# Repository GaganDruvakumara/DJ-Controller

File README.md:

# DIY DJ CONTROLLER
<body1 align="center">
  <br>

  <br>
  I’ve wanted to get into this hobby for a while, but the cost of entry was a major barrier. I looked through existing projects online, but I couldn’t find any open-source DJ controllers that really stood out. Many were small, limited, or designed more like experimental gadgets rather than something practical for real DJ use. There seemed to be a gap between expensive commercial controllers and accessible open-source alternatives, which inspired me to create this project.
  <br>
  <br>
  <i>This project is a fully open-source, 4-channel DIY DJ controller designed to be a functional and customizable alternative for anyone interested in building their own hardware.</i>
</body1>

# Key Features
* 4 Channel Deck
* XLR & 6.35MM Jack L&R master out + 3.5mm Jack L+R master out
* 3.5mm Jack headphone out
* 32-bit DAC for outputs
* 2 Neutrik Jack Mic Inputs
* 24-bit ADC for inputs
* 16 performance pad with mode selector
* 2 rotary encoders for menu navigation

# PCB
7x 2-layer PCBs (9 total including duplicates) designed in KiCad
### PCB Schematic

### PCB Front Layer

### PCB Back Layer

### PCB 3D View
Component models from GrabCad

## PCB Wiring Schematic

# CAD Assembly
CAD models designed in [Onshape](https://cad.onshape.com/documents/7791953f15b9474113af6284/w/087eac69f09fbec4411ed0d8/e/f1a33f0f3682f52a7b10a5d9?renderMode=0&uiState=6a372b9190a847a714621490).
Assembly done with M3x5x5 threaded inserts & M3 screws. Countersunk screws are used to attach the backplate, otherwise use pan head screws for everything else.

# Bill of Materials

|Part                                       |Min Qty.|Price Per Order|Approx. Cost|Link                                                |
|-------------------------------------------|--------|---------------|------------|----------------------------------------------------|
|                                           |        |               |            |                                                    |
|**Electronic Components**                      |        |               |            |                                                    |
|                                           |        |               |            |                                                    |
|Raspberry Pi Pico                          |1       |$3.00          |$3.00       |https://www.aliexpress.us/item/3256805941727857.html|
|MCP23017 I2C GPIO Expander                 |3       |$1.50          |$4.50       |https://www.aliexpress.us/item/3256809349179807.html|
|CD74HC4067M Multiplexer                    |2       |$4.00          |$4.00       |https://www.aliexpress.us/item/3256810617508863.html|
|PCM5012 Module                             |2       |$2.50          |$5.00       |https://www.aliexpress.us/item/3256806137563609.html|
|PCM1808 Module                             |1       |$2.00          |$2.00       |https://www.aliexpress.us/item/3256811975040160.html|
|EC11 Rotary Encoder Switch                 |2       |$2.50          |$5.00       |https://www.aliexpress.us/item/3256804936028561.html|
|4.7k THT Resistors                         |38      |$1.00          |$1.00       |https://www.aliexpress.us/item/3256802303553096.html|
|10k DOIT Rotary Potentiometers             |24      |$2.00          |$10.00      |https://www.aliexpress.us/item/3256809058182220.html|
|10K 60mm Slide Potentiometers (45mm travel)|7       |$2.00          |$14.00      |https://www.aliexpress.us/item/3256810149786178.html|
|600:600 Ohm Audio Transformers             |2       |$7.00          |$14.00      |https://www.aliexpress.us/item/3256811824890339.html|
|100 nF Ceramic Capacitors                  |6       |$1.00          |$1.00       |https://www.aliexpress.us/item/3256802104127109.html|
|100 uF Electrolytic Capacitors             |2       |$1.00          |$1.00       |https://www.aliexpress.us/item/3256807284223642.html|
|12mm Tacticle Switches                     |20      |$4.00          |$4.00       |https://www.aliexpress.us/item/2251832641145267.html|
|6mm Tacticle Switches                      |4       |$1.00          |$1.00       |https://www.aliexpress.us/item/2255800493650621.html|
|SPDT Slide Switch                          |2       |$2.00          |$2.00       |https://www.aliexpress.us/item/3256801114920515.html|
|WS2812B Individual RGB LEDs                |20      |$1.50          |$3.00       |https://www.aliexpress.us/item/2255801159561004.html|
|MT6701 Magnetic Rotary Encoder             |2       |$4.00          |$4.00       |https://www.aliexpress.us/item/3256810566166924.html|
|                                           |        |               |            |                                                    |
|                                           |        |               |            |                                                    |
|**IO Ports**                                   |        |               |            |                                                    |
|                                           |        |               |            |                                                    |
|XLR Male Panel Mount                       |2       |$1.00          |$2.00       |https://www.aliexpress.us/item/3256804030639653.html|
|6.35mm Jack Female Panel                   |2       |$2.00          |$4.00       |https://www.aliexpress.us/item/3256810292264986.html|
|Neutrik Combo Jack Panel                   |2       |$2.00          |$4.00       |https://www.aliexpress.us/item/3256801144687168.html|
|3.5mm Jack Female Panel                    |2       |$3.00          |$3.00       |https://www.aliexpress.us/item/3256804353386767.html|
|                                           |        |               |            |                                                    |
|                                           |        |               |            |                                                    |
|**Mechanical Components**                      |        |               |            |                                                    |
|                                           |        |               |            |                                                    |
|M3x5x5 Threaded inserts                    |32      |$4.00          |$4.00       |https://www.aliexpress.us/item/3256805892791659.html|
|M3x6 Pan Head Screws                       |18      |$2.00          |$2.00       |https://www.aliexpress.us/item/3256802178253461.html|
|M3x15(or 14) Pan Head Screws               |4       |$3.00          |$3.00       |https://www.aliexpress.us/item/3256802178253461.html|
|M3x6 Countersunk Screws                    |10      |$2.00          |$2.00       |https://www.aliexpress.us/item/3256808642166413.html|
|6x2mm Radial Magnet                        |2       |$6.00          |$6.00       |https://www.aliexpress.us/item/3256810512258917.html|
|608ZZ Bearing                              |2       |$2.00          |$2.00       |https://www.aliexpress.us/item/3256807356386819.html|
|                                           |        |               |            |                                                    |
|                                           |        |               |            |                                                    |
|**Total Estimated Cost**                       |        |               |$110.50     |                                                    |

### JLC PCB Order:

# Firmware

WIP

### Libraries
* Raspberry Pi Pico SDK C/C++
* Raspberry Pi Pico VS Code Extension

# Credits
* [Onshape](https://www.onshape.com/en/)
* [KiCad](https://www.kicad.org)
* [GrabCad](https://grabcad.com)

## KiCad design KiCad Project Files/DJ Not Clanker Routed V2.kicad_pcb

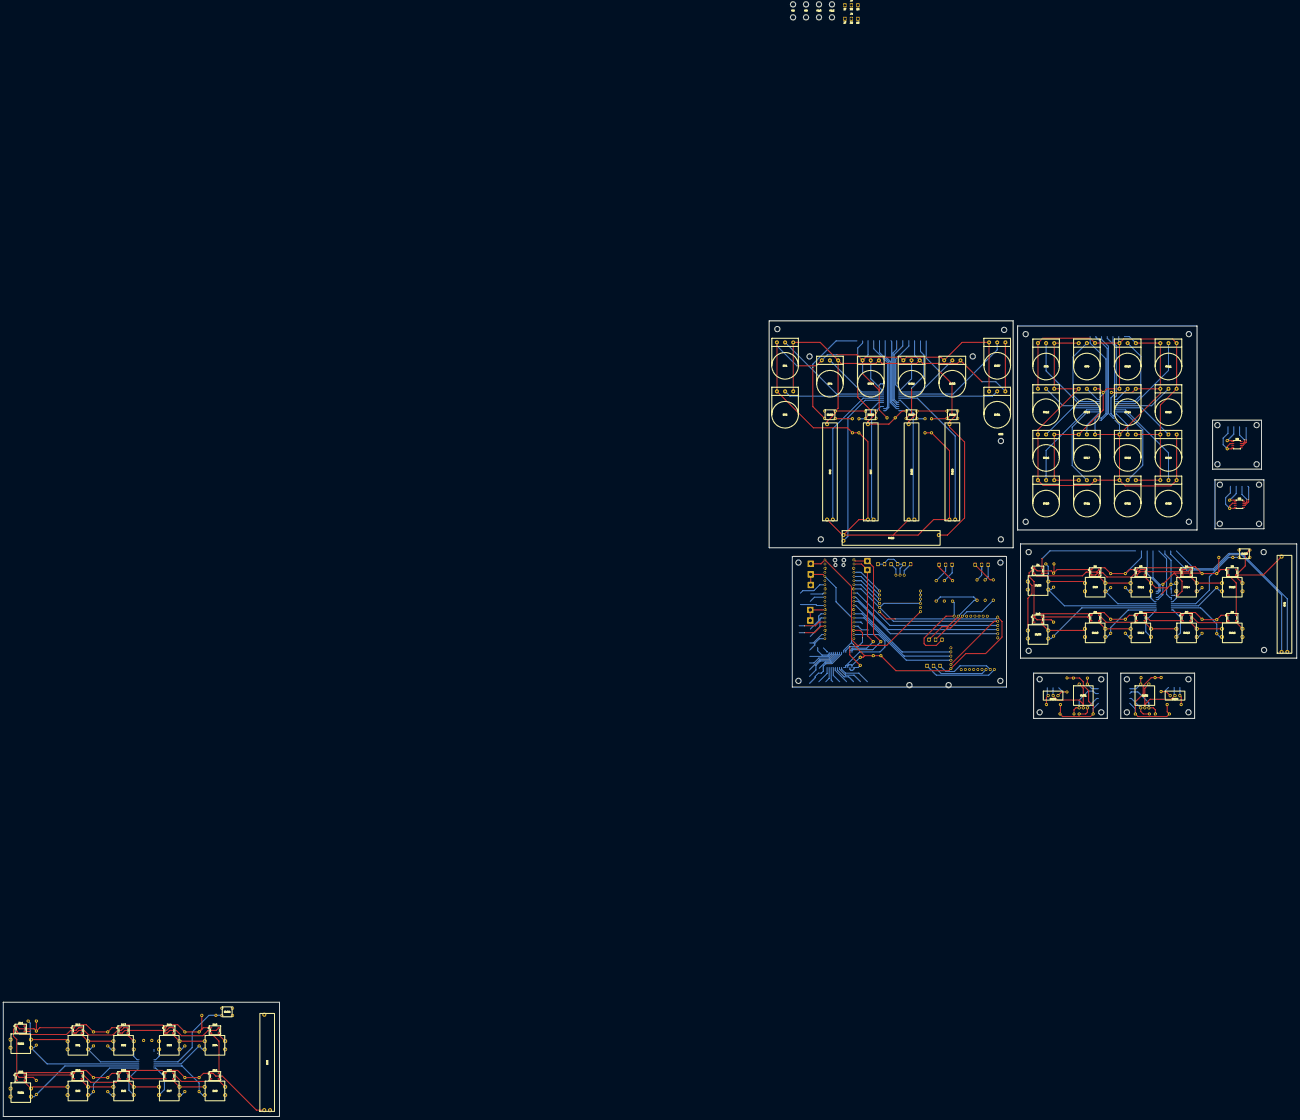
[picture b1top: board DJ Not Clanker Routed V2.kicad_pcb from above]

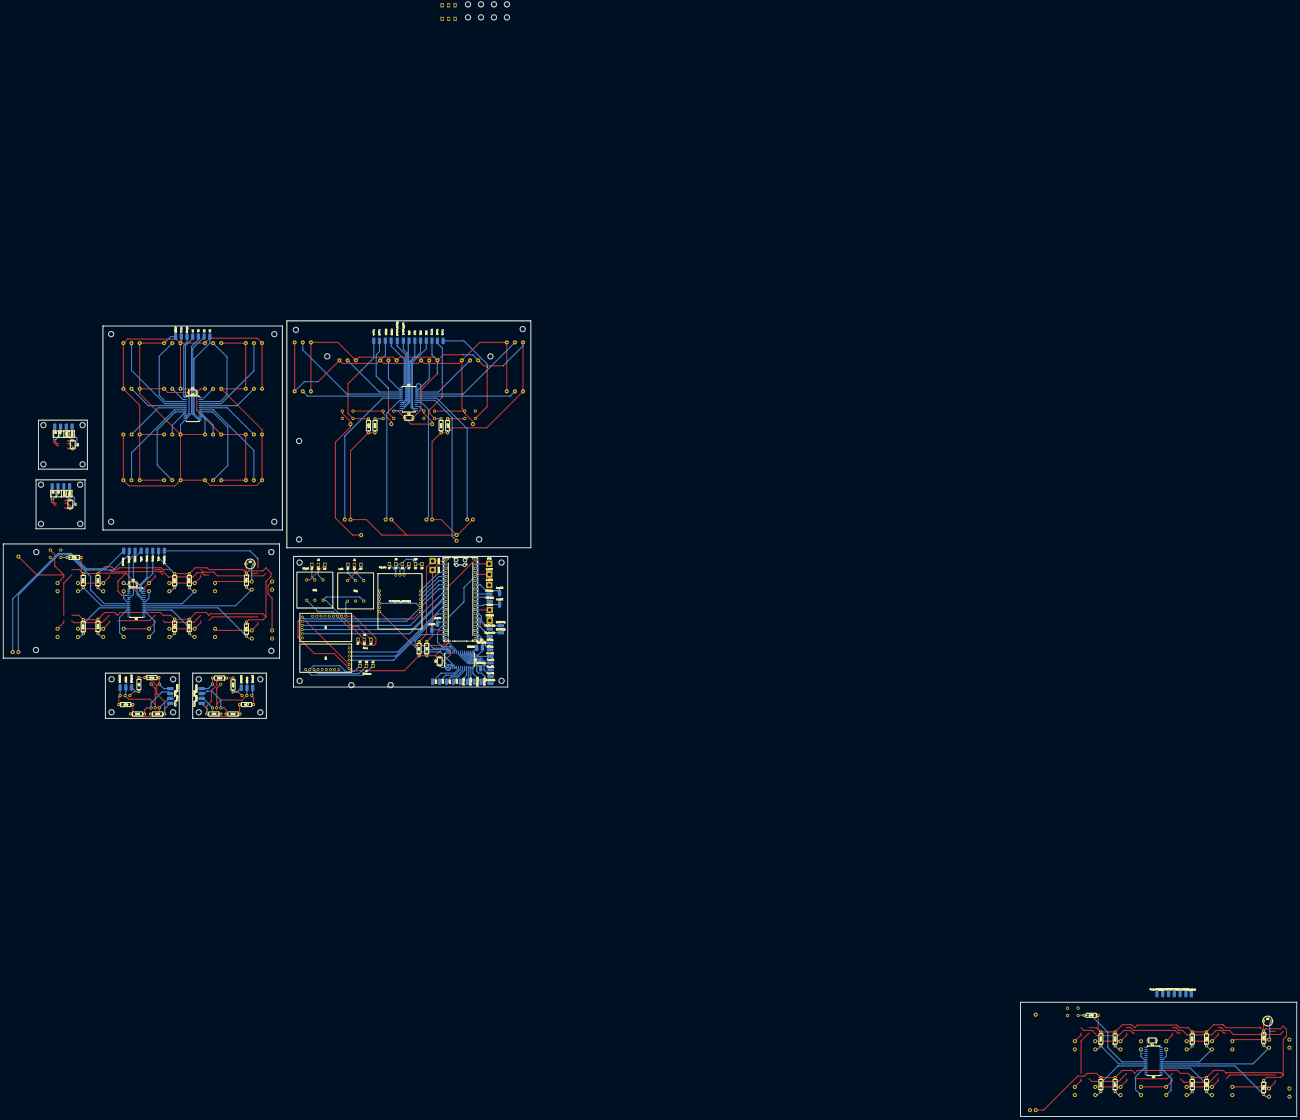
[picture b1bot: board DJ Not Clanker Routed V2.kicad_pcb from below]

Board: 2 copper layers, 792.6 x 487.6 mm, 286 parts (156 on the bottom side), 172 nets.

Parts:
3.3V1, 5V1: SolderWirePad_1x01_SMD_2x4mm
3.3V2, 3.3V3, 5V2: SolderWire-1.5sqmm_1x01_D1.7mm_OD3.9mm
A1: RaspberryPi_Pico; RaspberryPi_Pico_Common_Unspecified
A2, A3: SolderWirePad_1x01_SMD_2x4mm
B1, B2: SolderWirePad_1x01_SMD_2x4mm
C1, C2, C3, C4, C7, C8, C9: 0.1uF; MLCC Cap
C5, C6: 100uF; Electrolytic Cap
COM1, COM2, COM11, COM21: SolderWirePad_1x01_SMD_2x4mm
Cue1, Cue2, Cue3, Cue4, Cue11, Cue21, Cue31, Cue41: SolderWirePad_1x01_SMD_2x4mm
D1, D2, D3, D4, D5, D6, D7, D8, D9, D10, D11, D12, D13, D14, D15, D16, D17, D18, D19, D20: WS2812B; LED_WS2812B_PLCC4_5.0x5.0mm_P3.2mm
DSSW1, DSSW2, DSSW3, DSSW4, DSSW11, DSSW21, DSSW31, DSSW41: SolderWirePad_1x01_SMD_2x4mm
Fader1: SolderWirePad_1x01_SMD_2x4mm
FaderRight1: SolderWirePad_1x01_SMD_2x4mm
GND1, GND2, GND3, GND4, GND5, GND6, GND7, GND8: SolderWirePad_1x01_SMD_2x4mm
GND9, GND10: SolderWire-1.5sqmm_1x01_D1.7mm_OD3.9mm
H1, H2, H3, H4, H5, H5#2, H6, H6#2, H7, H7#2, H8, H8#2, H9, H9#2, H10, H10#2, H11, H11#2, H12, H12#2, H13, H14, H15, H16, H17, H18, H19, H20, H21, H22, H23, H24, H25, H26, H27, H28, H29, H30, H31, H32, H33, H34, H35, H36, H37: MountingHole; MountingHole_3.2mm_M3
INT1, INT2, INT11, INT21: SolderWirePad_1x01_SMD_2x4mm
J1, J2: XLR3; XLR_TRS Audio Pads
J3, J4: AudioJack3; XLR_TRS Audio Pads
J7, J9: AudioJack3; TRS Audio Pads
J8, J10: XLR3_AudioJack3_Combo; XLR_TRS Audio Pads
JogA1, JogA2: SolderWirePad_1x01_SMD_2x4mm
JogB1, JogB2: SolderWirePad_1x01_SMD_2x4mm
LeftFader1: SolderWirePad_1x01_SMD_2x4mm
Lights1, Lights2, Lights11, Lights21: SolderWirePad_1x01_SMD_2x4mm
PCM1808_BOARD1: PCM1808_Module
R5, R6, R9, R10, R11, R12, R13, R14, R15, R16, R17, R18, R19, R20, R21, R22, R23, R24, R25, R26, R27, R28, R29, R30, R31, R32, R33, R34, R35, R36, R37, R38, R43, R44, R45, R46, R47, R48: R4.7k; Resistor
REA1, REA2, REA12, REA22: SolderWirePad_1x01_SMD_2x4mm
REB1, REB2, REB12, REB22: SolderWirePad_1x01_SMD_2x4mm
RESW1, RESW2, RESW12, RESW22: SolderWirePad_1x01_SMD_2x4mm
RV1, RV4, RV5, RV8, RV9, RV10, RV11, RV12, RV13, RV14, RV15, RV16, RV17, RV18, RV19, RV20, RV21, RV22, RV23, RV24, RV26, RV27, RV30, RV31: Pot; DOIT WL Rotary Pot
RV2, RV3, RV6, RV7, RV25, RV28, RV29: Fader; 60MM Length Fader Pot
RightFader1: SolderWirePad_1x01_SMD_2x4mm
S0, S1, S02, S2, S3, S03, S12, S13, S22, S23, S32, S33: SolderWirePad_1x01_SMD_2x4mm
SCK1, SCK2: SolderWirePad_1x01_SMD_2x4mm
SCK3: SolderWire-1.5sqmm_1x01_D1.7mm_OD3.9mm
SDA1, SDA2: SolderWirePad_1x01_SMD_2x4mm
SDA3: SolderWire-1.5sqmm_1x01_D1.7mm_OD3.9mm
SW1, SW2, SW3, SW4, SW5, SW6, SW7, SW8, SW9, SW10, SW11, SW12, SW13, SW14, SW15, SW16, SW21, SW22, SW30, SW33: SW_Push; 12mm Tactile Switch
SW23, SW24, SW27, SW28, SW29, SW35: SW_Push; 6mm Tactile Switch
SW31, SW32: RotaryEncoder_Switch; EC11 Encoder Switch
SW37, SW38: SW_SPDT; SS-12F44-GXXX SPDT SW
TR1, TR2: TRANSF5; E-9818 Audio Transformer
U1, U2, U4: MCP23017x-x-SO; SOIC-28W_7.5x17.9mm_P1.27mm
U3, U7: CD74HC4067M; SOIC-24W_7.5x15.4mm_P1.27mm
U5, U6: PCM5102 Module; GY-PCM5102 DAC
U8, U9: MT6701CT; SO-8_3.9x4.9mm_P1.27mm
VCC1, VCC2, VCC3, VCC4: SolderWirePad_1x01_SMD_2x4mm
VDD1, VDD2, VDD4: SolderWirePad_1x01_SMD_2x4mm

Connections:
+3.3V: 3.3V1.1, 3.3V2.1, 3.3V3.1, A1.36 (3V3), C1.1, C2.1, C4.1, C9.1, PCM1808_BOARD1.12 (3.3V), R5.1, R6.1, R9.1, R10.1, R11.1, R13.1, R15.1, R17.1, R18.1, R19.2, R20.2, R21.2, R22.2, R23.2, R24.2, R25.2, R26.2, R27.2, R28.2, R37.2, R38.2, R43.1, R44.1, R45.2, R46.1, R47.2, R48.1, RV1.1, RV2.1, RV3.1, RV4.1, RV5.1, RV6.1, RV7.1, RV8.1, RV9.3, RV10.1, RV11.3, RV12.1, RV13.3, RV14.1, RV15.3, RV16.3, RV17.1, RV18.3, RV19.1, RV20.3, RV21.1, RV22.3, RV23.1, RV24.1, RV25.1, RV26.1, RV27.1, RV28.1, RV29.1, RV30.1, RV31.1, U2.9 (V_{DD}), U2.15 (A0), U2.18 (~RESET), U3.24 (VCC), U4.9 (V_{DD}), U4.16 (A1), U4.18 (~RESET), U5.6 (VIN), U6.6 (VIN), U7.24 (VCC), VCC1.1, VCC2.1, VCC3.1, VCC4.1, VDD4.1
+5V: 5V1.1, 5V2.1, A1.40 (VBUS), C3.1, C5.1, C6.1, D1.1 (VDD), D2.1 (VDD), D3.1 (VDD), D4.1 (VDD), D5.1 (VDD), D6.1 (VDD), D7.1 (VDD), D8.1 (VDD), D9.1 (VDD), D10.1 (VDD), D11.1 (VDD), D12.1 (VDD), D13.1 (VDD), D14.1 (VDD), D15.1 (VDD), D16.1 (VDD), D17.1 (VDD), D18.1 (VDD), D19.1 (VDD), D20.1 (VDD), PCM1808_BOARD1.6 (+5V), R12.1, R14.1, R16.1, R29.2, R30.2, R31.2, R32.2, R33.2, R34.2, R35.2, R36.2, U1.9 (V_{DD}), U1.18 (~RESET)
/COM: A1.32 (GPIO27_ADC1), COM21.1
/COM_1: A1.31 (GPIO26_ADC0), COM11.1
/DAC Outputs/MBCK: A1.11 (GPIO8), U6.2 (BCK)
/DAC Outputs/MDIN: A1.10 (GPIO7), U6.3 (DIN)
/DAC Outputs/MLRCK: A1.9 (GPIO6), U6.4 (LRCK)
/DAC Outputs/PBCK: A1.12 (GPIO9), U5.2 (BCK)
/DAC Outputs/PDIN: A1.14 (GPIO10), U5.3 (DIN)
/DAC Outputs/PLRCK: A1.15 (GPIO11), U5.4 (LRCK)
/INT1: A1.21 (GPIO16), INT11.1
/INT2: A1.22 (GPIO17), INT21.1
/Mic Inputs/BCK: A1.4 (GPIO2), PCM1808_BOARD1.7 (BCK)
/Mic Inputs/LRC: A1.6 (GPIO4), PCM1808_BOARD1.9 (LRC)
/Mic Inputs/OUT: A1.5 (GPIO3), PCM1808_BOARD1.8 (OUT)
/Mic Inputs/SCK: A1.7 (GPIO5), PCM1808_BOARD1.10 (SCK)
/Misc Switches/CueB: R13.2, SW22.2, U2.6 (GPB5)
/Misc Switches/CueCh3: Cue3.1, R19.1, SW27.2
/Misc Switches/CueCh4: Cue4.1, R20.1, SW28.2
/Misc Switches/Deck Select 2: DSSW2.1, R9.2, SW37.1 (A)
/Misc Switches/Deck Select 4: DSSW4.1, R10.2, SW37.3 (C)
/Misc Switches/PModeB: R15.2, SW24.2, U2.22 (GPA1)
/Misc Switches/PlayB: R11.2, SW21.2, U2.5 (GPB4)
/Misc Switches/SW_R1: R21.1, SW1.2, U2.7 (GPB6)
/Misc Switches/SW_R2: R22.1, SW2.2, U2.8 (GPB7)
/Misc Switches/SW_R3: R23.1, SW3.2, U2.21 (GPA0)
/Misc Switches/SW_R4: R24.1, SW4.2, U2.23 (GPA2)
/Misc Switches/SW_R5: R25.1, SW5.2, U2.4 (GPB3)
/Misc Switches/SW_R6: R26.1, SW6.2, U2.3 (GPB2)
/Misc Switches/SW_R7: R27.1, SW7.2, U2.25 (GPA4)
/Misc Switches/SW_R8: R28.1, SW8.2, U2.24 (GPA3)
/Performance Pads I2C/CueA: R14.2, SW33.2, U1.6 (GPB5)
/Performance Pads I2C/CueCh1: Cue1.1, R37.1, SW29.2
/Performance Pads I2C/CueCh2: Cue2.1, R38.1, SW35.2
/Performance Pads I2C/Deck Select 1: DSSW1.1, R17.2, SW38.1 (A)
/Performance Pads I2C/Deck Select 3: DSSW3.1, R18.2, SW38.3 (C)
/Performance Pads I2C/PModeA: R16.2, SW23.2, U1.22 (GPA1)
/Performance Pads I2C/PlayA: R12.2, SW30.2, U1.5 (GPB4)
/Performance Pads I2C/SW_L1: R29.1, SW9.2, U1.7 (GPB6)
/Performance Pads I2C/SW_L2: R30.1, SW11.2, U1.8 (GPB7)
/Performance Pads I2C/SW_L3: R31.1, SW14.2, U1.21 (GPA0)
/Performance Pads I2C/SW_L4: R32.1, SW15.2, U1.23 (GPA2)
/Performance Pads I2C/SW_L5: R33.1, SW10.2, U1.4 (GPB3)
/Performance Pads I2C/SW_L6: R34.1, SW12.2, U1.3 (GPB2)
/Performance Pads I2C/SW_L7: R35.1, SW13.2, U1.25 (GPA4)
/Performance Pads I2C/SW_L8: R36.1, SW16.2, U1.24 (GPA3)
/S0: S03.1, U4.21 (GPA0)
/S1: S13.1, U4.22 (GPA1)
/S2: S23.1, U4.23 (GPA2)
/S3: S33.1, U4.24 (GPA3)
/SCK: A1.2 (GPIO1), R6.2, SCK3.1, U4.12 (SCK)
/SDA: A1.1 (GPIO0), R5.2, SDA3.1, U4.13 (SDA)
GND: A1.3 (GND), A1.8 (GND), A1.13 (GND), A1.18 (GND), A1.23 (GND), A1.28 (GND), A1.38 (GND), C1.2, C2.2, C3.2, C4.2, C5.2, C6.2, C9.2, D1.3 (VSS), D2.3 (VSS), D3.3 (VSS), D4.3 (VSS), D5.3 (VSS), D6.3 (VSS), D7.3 (VSS), D8.3 (VSS), D9.3 (VSS), D10.3 (VSS), D11.3 (VSS), D12.3 (VSS), D13.3 (VSS), D14.3 (VSS), D15.3 (VSS), D16.3 (VSS), D17.3 (VSS), D18.3 (VSS), D19.3 (VSS), D20.3 (VSS), GND3.1, GND4.1, GND5.1, GND6.1, GND7.1, GND8.1, GND9.1, GND10.1, PCM1808_BOARD1.1 (FMY), PCM1808_BOARD1.2 (MD1), PCM1808_BOARD1.3 (MD0), PCM1808_BOARD1.4 (GND), PCM1808_BOARD1.11 (GND), RV1.3, RV2.3, RV3.3, RV4.3, RV5.3, RV6.3, RV7.3, RV8.3, RV9.1, RV10.3, RV11.1, RV12.3, RV13.1, RV14.3, RV15.1, RV16.1, RV17.3, RV18.1, RV19.3, RV20.1, RV21.3, RV22.1, RV23.3, RV24.3, RV25.3, RV26.3, RV27.3, RV28.3, RV29.3, RV30.3, RV31.3, SW1.1, SW2.1, SW3.1, SW4.1, SW5.1, SW6.1, SW7.1, SW8.1, SW9.1, SW10.1, SW11.1, SW12.1, SW13.1, SW14.1, SW15.1, SW16.1, SW21.1, SW22.1, SW23.1, SW24.1, SW27.1, SW28.1, SW29.1, SW30.1, SW31.C, SW31.S1, SW32.C, SW32.S2, SW33.1, SW35.1, SW37.2 (B), SW38.2 (B), U1.10 (V_{SS}), U1.15 (A0), U1.16 (A1), U1.17 (A2), U2.10 (V_{SS}), U2.16 (A1), U2.17 (A2), U3.12 (GND), U3.15 (~E), U4.10 (V_{SS}), U4.15 (A0), U4.17 (A2), U5.5 (GND), U6.5 (GND), U7.12 (GND), U7.15 (~E)
unnamed: A1.16 (GPIO12), JogA1.1
unnamed: A1.17 (GPIO13), JogB1.1
unnamed: A1.19 (GPIO14), U4.19 (INTB), U4.20 (INTA)
unnamed: A1.24 (GPIO18), DSSW21.1
unnamed: A1.25 (GPIO19), DSSW41.1
unnamed: A1.26 (GPIO20), Lights21.1
unnamed: A1.27 (GPIO21), Lights11.1
unnamed: A1.29 (GPIO22), JogA2.1
unnamed: A1.34 (GPIO28_ADC2), JogB2.1
unnamed: D1.4 (DIN), Lights1.1
unnamed: D1.2 (DOUT), D2.4 (DIN)
unnamed: D2.2 (DOUT), D3.4 (DIN)
unnamed: D3.2 (DOUT), D4.4 (DIN)
unnamed: D4.2 (DOUT), D5.4 (DIN)
unnamed: D5.2 (DOUT), D6.4 (DIN)
unnamed: D6.2 (DOUT), D7.4 (DIN)
unnamed: D7.2 (DOUT), D8.4 (DIN)
unnamed: D8.2 (DOUT), D9.4 (DIN)
unnamed: D9.2 (DOUT), D10.4 (DIN)
unnamed: D11.4 (DIN), Lights2.1
unnamed: D11.2 (DOUT), D12.4 (DIN)
unnamed: D12.2 (DOUT), D13.4 (DIN)
unnamed: D13.2 (DOUT), D14.4 (DIN)
unnamed: D14.2 (DOUT), D15.4 (DIN)
unnamed: D15.2 (DOUT), D16.4 (DIN)
unnamed: D16.2 (DOUT), D17.4 (DIN)
unnamed: D17.2 (DOUT), D18.4 (DIN)
unnamed: D18.2 (DOUT), D19.4 (DIN)
unnamed: D19.2 (DOUT), D20.4 (DIN)
unnamed: Fader1.1, RV2.2
unnamed: FaderRight1.1, RV6.2
unnamed: J1.1, TR1.5
unnamed: J1.2, TR1.4
unnamed: J1.3, TR1.6
unnamed: J2.1, TR2.5
unnamed: J2.2, TR2.4
unnamed: J2.3, TR2.6
unnamed: J7.S, U5.14 (AGND)
unnamed: J9.S, TR1.1, TR2.1, U6.14 (AGND)
unnamed: J8.1, J8.3, J10.1, J10.3, PCM1808_BOARD1.14 (-)
unnamed: J10.2, PCM1808_BOARD1.15 (LIN)
unnamed: J8.2, PCM1808_BOARD1.13 (RIN)
unnamed: R43.2, RESW2.1, SW31.S2
unnamed: R44.2, RESW1.1, SW32.S1
unnamed: R45.1, REB1.1, SW32.B
unnamed: R46.2, REA1.1, SW32.A
unnamed: R47.1, REB2.1, SW31.B
unnamed: R48.2, REA2.1, SW31.A
unnamed: INT1.1, U1.19 (INTB), U1.20 (INTA)
unnamed: SCK1.1, U1.12 (SCK)
unnamed: SDA1.1, U1.13 (SDA)
unnamed: INT2.1, U2.19 (INTB), U2.20 (INTA)
unnamed: SCK2.1, U2.12 (SCK)
unnamed: SDA2.1, U2.13 (SDA)
unnamed: COM1.1, U3.1 (COM)
unnamed: RV18.2, U3.9 (I0)
unnamed: RV22.2, U3.8 (I1)
unnamed: RV23.2, U3.7 (I2)
unnamed: RV19.2, U3.6 (I3)
unnamed: RV15.2, U3.5 (I4)
unnamed: RV11.2, U3.4 (I5)
unnamed: RV10.2, U3.3 (I6)
unnamed: RV14.2, U3.2 (I7)
unnamed: RV13.2, U3.23 (I8)
unnamed: RV9.2, U3.22 (I9)
unnamed: RV8.2, U3.21 (I10)
unnamed: RV12.2, U3.20 (I11)
unnamed: RV16.2, U3.19 (I12)
unnamed: RV20.2, U3.18 (I13)
unnamed: RV21.2, U3.17 (I14)
unnamed: RV17.2, U3.16 (I15)
unnamed: S0.1, U3.10 (S0)
unnamed: S1.1, U3.11 (S1)
unnamed: S2.1, U3.14 (S2)
unnamed: S3.1, U3.13 (S3)
unnamed: REA12.1, U4.25 (GPA4)
unnamed: REB12.1, U4.26 (GPA5)
unnamed: RESW12.1, U4.27 (GPA6)
unnamed: REB22.1, U4.28 (GPA7)
unnamed: REA22.1, U4.1 (GPB0)
unnamed: RESW22.1, U4.2 (GPB1)
unnamed: Cue11.1, U4.3 (GPB2)
unnamed: Cue21.1, U4.4 (GPB3)
unnamed: Cue31.1, U4.5 (GPB4)
unnamed: Cue41.1, U4.6 (GPB5)
unnamed: DSSW11.1, U4.7 (GPB6)
unnamed: DSSW31.1, U4.8 (GPB7)
unnamed: J7.T, U5.15 (LROUT)
unnamed: J7.R, U5.13 (ROUT)
unnamed: J9.T, TR1.3, U6.15 (LROUT)
unnamed: J9.R, TR2.3, U6.13 (ROUT)
unnamed: COM2.1, U7.1 (COM)
unnamed: LeftFader1.1, U7.9 (I0)
unnamed: RightFader1.1, U7.8 (I1)
unnamed: RV25.2, U7.7 (I2)
unnamed: RV29.2, U7.6 (I3)
unnamed: RV31.2, U7.5 (I4)
unnamed: RV27.2, U7.4 (I5)
unnamed: RV30.2, U7.3 (I6)
unnamed: RV26.2, U7.2 (I7)
unnamed: RV24.2, U7.23 (I8)
unnamed: RV4.2, U7.22 (I9)
unnamed: RV1.2, U7.21 (I10)
unnamed: RV5.2, U7.20 (I11)
unnamed: RV3.2, U7.19 (I12)
unnamed: RV28.2, U7.18 (I13)
unnamed: RV7.2, U7.17 (I14)
unnamed: S02.1, U7.10 (S0)
unnamed: S12.1, U7.11 (S1)
unnamed: S22.1, U7.14 (S2)
unnamed: S32.1, U7.13 (S3)
unnamed: A3.1, U8.6 (A)
unnamed: B2.1, U8.7 (B)
unnamed: C7.2, GND2.1, U8.2 (MODE), U8.4 (GND)
unnamed: C7.1, U8.1 (VDD), VDD2.1
unnamed: A2.1, U9.6 (A)
unnamed: B1.1, U9.7 (B)
unnamed: C8.2, GND1.1, U9.2 (MODE), U9.4 (GND)
unnamed: C8.1, U9.1 (VDD), VDD1.1

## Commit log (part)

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2026-06-20 added Cad files
2026-06-20 added lots of files
2026-06-20 Update README with project title and features
    Added project title and key features to README.
2026-06-20 Fix formatting in README for DIY DJ Controller
    Updated formatting and structure in README.md.
2026-06-20 Fix formatting issues in README.md
2026-06-21 Add PCB section with schematic to README
    Added PCB section with schematic image to README.
2026-06-21 Enhance README with PCB and CAD details
    Added detailed PCB schematics and CAD assembly images.
2026-06-21 Update README with firmware section and credits
    Added credits section and improved formatting.
2026-06-21 added zine
2026-06-21 updated zine
2026-06-21 added zine png
2026-06-21 Change image source for DJ Controller
    Updated image source link in README.md.
2026-06-21 added firmware
2026-06-21 updated firmware
2026-06-21 updated BOM
2026-06-21 Enhance README with project motivation details
    Added a personal motivation section to the project description.
2026-06-21 Revise README project description
    Rearranged project description for clarity.
2026-06-21 Update README with PCB Back Layer and 3D View
    Added PCB Back Layer and PCB 3D View sections with images.
2026-06-21 Revise project motivation in README
    Reworded introduction to clarify motivation for project.
2026-06-21 Enhance README with project overview and features
    Added a project description highlighting its open-source nature and functionality as a DIY DJ controller.
2026-06-21 Italicize project description in README
    Italicize project description for emphasis.
2026-06-21 Update README with Libraries section
    Added a section for Libraries under Firmware in README.
2026-06-22 updated BOM format from TSV to CSV
2026-06-22 Add Bill of Materials to README
    Added a Bill of Materials section with detailed parts list including quantities, prices, and links.
2026-06-22 Fix formatting issues in component list table
2026-06-22 Update Bill of Materials with new sections
2026-06-22 Update Bill of Materials section in README
2026-06-22 Bold section headers in README.md
2026-06-22 Update README with project details and features
2026-06-22 Fix formatting issues in BOM.csv
    Removed extra spaces in the BOM.csv file and ensured consistent formatting for prices and links.
2026-06-22 Clarify assembly instructions in README
    Added details about screw types for assembly.
